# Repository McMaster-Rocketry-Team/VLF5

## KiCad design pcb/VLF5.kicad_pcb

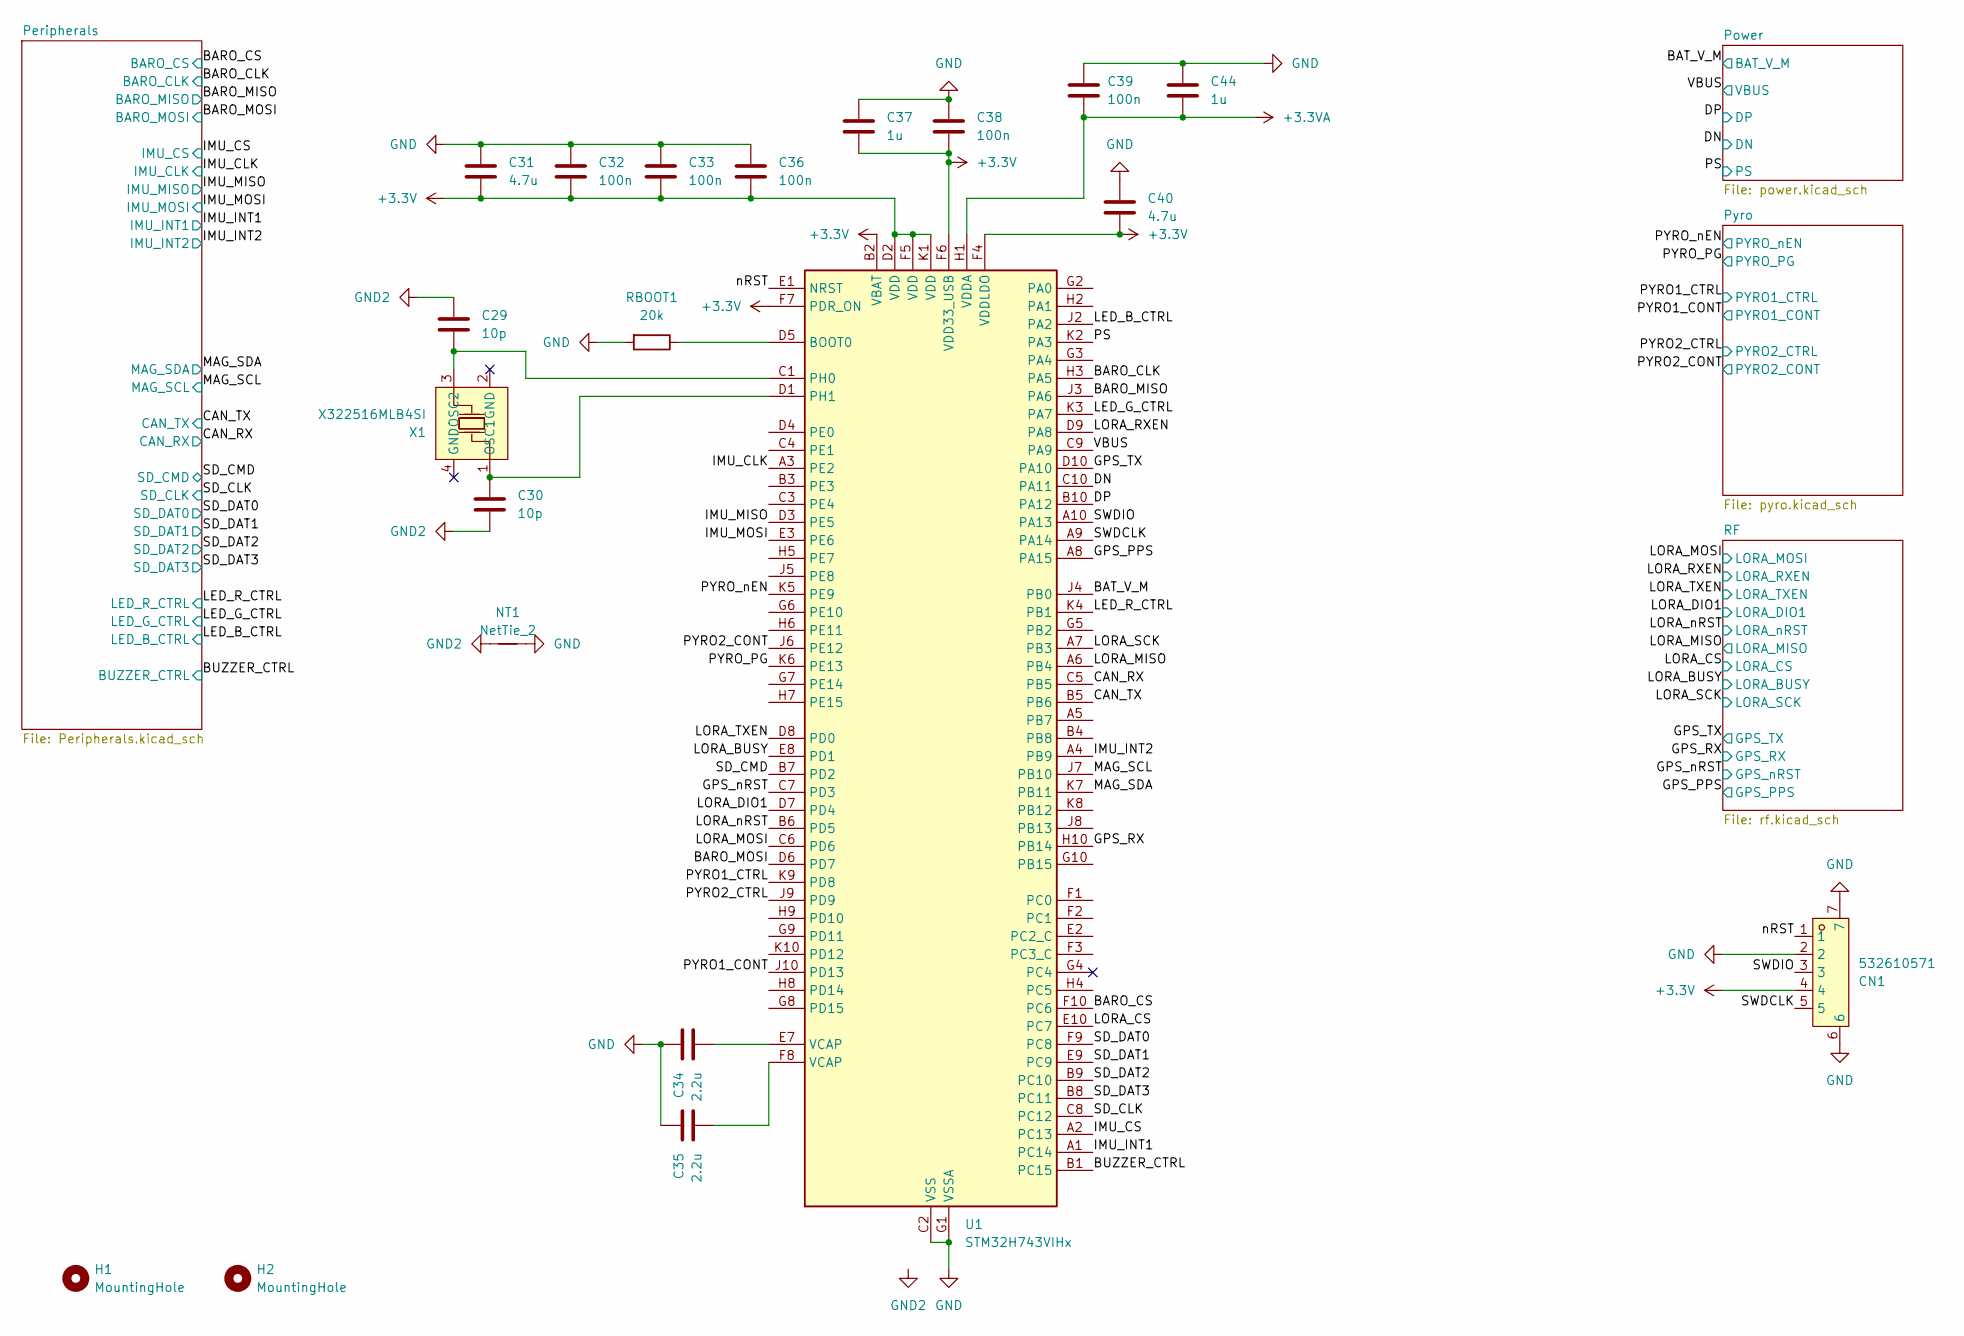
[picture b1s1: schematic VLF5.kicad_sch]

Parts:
C29, C30: 10p; C_0402_1005Metric
C31, C40: 4.7u; C_0402_1005Metric
C32, C33, C36, C38, C39: 100n; C_0402_1005Metric
C34, C35: 2.2u; C_0402_1005Metric
C37, C44: 1u; C_0402_1005Metric
CN1: 532610571; CONN-SMD_5P-P1.25_532610571-2; LCSC Part C392176
H1, H2: MountingHole; MountingHole_2.7mm_M2.5
NT1: NetTie_2; NetTie-2_SMD_Pad0.5mm
RBOOT1: 20k; R_0402_1005Metric
U1: STM32H743VIHx; TFBGA-100_8x8mm_Layout10x10_P0.8mm
X1: X322516MLB4SI; OSC-SMD_4P-L3.2-W2.5-BL; LCSC Part C13738

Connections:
+3.3V: C31.2, C32.2, C33.2, C36.2, C37.2, C38.2, C40.2, CN1.4, U1.B2 (VBAT), U1.D2 (VDD), U1.F4 (VDDLDO), U1.F5 (VDD), U1.F6 (VDD33_USB), U1.F7 (PDR_ON), U1.K1 (VDD); also elsewhere on the board
+3.3VA: C39.2, C44.2, U1.H1 (VDDA); also elsewhere on the board
/BARO_CLK: U1.H3 (PA5); also elsewhere on the board
/BARO_CS: U1.F10 (PC6); also elsewhere on the board
/BARO_MISO: U1.J3 (PA6); also elsewhere on the board
/BARO_MOSI: U1.D6 (PD7); also elsewhere on the board
/BAT_V_M: U1.J4 (PB0); also elsewhere on the board
/BUZZER_CTRL: U1.B1 (PC15); also elsewhere on the board
/CAN_RX: U1.C5 (PB5); also elsewhere on the board
/CAN_TX: U1.B5 (PB6); also elsewhere on the board
/DN: U1.C10 (PA11); also elsewhere on the board
/DP: U1.B10 (PA12); also elsewhere on the board
/GPS_PPS: U1.A8 (PA15); also elsewhere on the board
/GPS_RX: U1.H10 (PB14); also elsewhere on the board
/GPS_TX: U1.D10 (PA10); also elsewhere on the board
/GPS_nRST: U1.C7 (PD3); also elsewhere on the board
/IMU_CLK: U1.A3 (PE2); also elsewhere on the board
/IMU_CS: U1.A2 (PC13); also elsewhere on the board
/IMU_INT1: U1.A1 (PC14); also elsewhere on the board
/IMU_INT2: U1.A4 (PB9); also elsewhere on the board
/IMU_MISO: U1.D3 (PE5); also elsewhere on the board
/IMU_MOSI: U1.E3 (PE6); also elsewhere on the board
/LED_B_CTRL: U1.J2 (PA2); also elsewhere on the board
/LED_G_CTRL: U1.K3 (PA7); also elsewhere on the board
/LED_R_CTRL: U1.K4 (PB1); also elsewhere on the board
/LORA_BUSY: U1.E8 (PD1); also elsewhere on the board
/LORA_CS: U1.E10 (PC7); also elsewhere on the board
/LORA_DIO1: U1.D7 (PD4); also elsewhere on the board
/LORA_MISO: U1.A6 (PB4); also elsewhere on the board
/LORA_MOSI: U1.C6 (PD6); also elsewhere on the board
/LORA_RXEN: U1.D9 (PA8); also elsewhere on the board
/LORA_SCK: U1.A7 (PB3); also elsewhere on the board
/LORA_TXEN: U1.D8 (PD0); also elsewhere on the board
/LORA_nRST: U1.B6 (PD5); also elsewhere on the board
/MAG_SCL: U1.J7 (PB10); also elsewhere on the board
/MAG_SDA: U1.K7 (PB11); also elsewhere on the board
/PS: U1.K2 (PA3); also elsewhere on the board
/PYRO1_CONT: U1.J10 (PD13); also elsewhere on the board
/PYRO1_CTRL: U1.K9 (PD8); also elsewhere on the board
/PYRO2_CONT: U1.J6 (PE12); also elsewhere on the board
/PYRO2_CTRL: U1.J9 (PD9); also elsewhere on the board
/PYRO_PG: U1.K6 (PE13); also elsewhere on the board
/PYRO_nEN: U1.K5 (PE9); also elsewhere on the board
/SD_CLK: U1.C8 (PC12); also elsewhere on the board
/SD_CMD: U1.B7 (PD2); also elsewhere on the board
/SD_DAT0: U1.F9 (PC8); also elsewhere on the board
/SD_DAT1: U1.E9 (PC9); also elsewhere on the board
/SD_DAT2: U1.B9 (PC10); also elsewhere on the board
/SD_DAT3: U1.B8 (PC11); also elsewhere on the board
/SWDCLK: CN1.5, U1.A9 (PA14)
/SWDIO: CN1.3, U1.A10 (PA13)
/VBUS: U1.C9 (PA9); also elsewhere on the board
/nRST: CN1.1, U1.E1 (NRST)
unnamed: C34.2, U1.E7 (VCAP)
unnamed: C35.2, U1.F8 (VCAP)
unnamed: RBOOT1.1, U1.D5 (BOOT0)
unnamed: C29.2, U1.C1 (PH0), X1.3 (OSC2)
unnamed: C30.1, U1.D1 (PH1), X1.1 (OSC1)

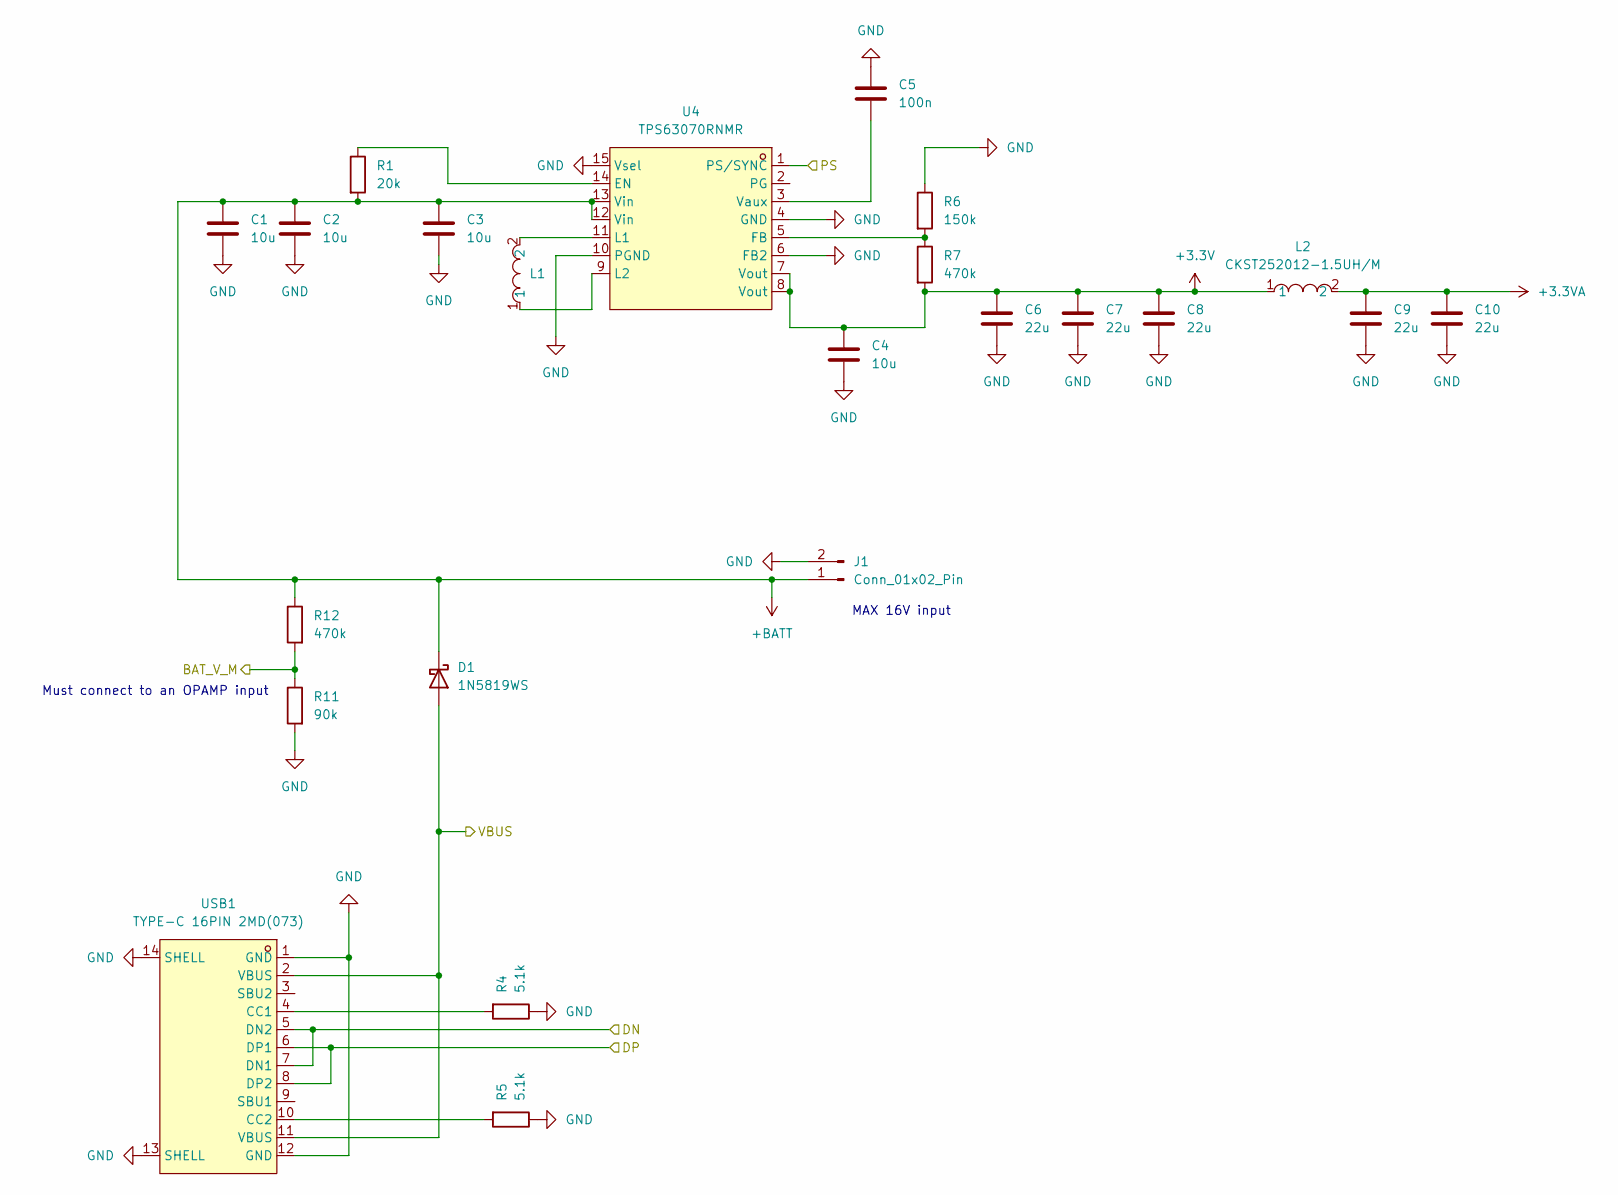
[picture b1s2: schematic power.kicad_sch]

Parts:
C1, C2, C3, C4: 10u; C_0603_1608Metric
C5: 100n; C_0402_1005Metric
C6, C7, C8, C9, C10: 22u; C_0603_1608Metric
D1: 1N5819WS; D_SOD-323
J1: Conn_01x02_Pin; 1054301102
L1, L2: CKST252012-1.5UH/M; IND-SMD_L2.5-W2.0-VLS252012CX-150M; LCSC Part C3002550
R1: 20k; R_0402_1005Metric
R4, R5: 5.1k; R_0402_1005Metric
R6: 150k; R_0402_1005Metric
R7, R12: 470k; R_0402_1005Metric
R11: 90k; R_0402_1005Metric
U4: TPS63070RNMR; VQFN-HR-15_L3.0-W2.5-P0.50-BL_TPS63070RNMR; LCSC Part C109322
USB1: TYPE-C 16PIN 2MD(073); USB-C-SMD_TYPE-C-6PIN-2MD-073; LCSC Part C2765186

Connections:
+3.3V: C4.2, C6.2, C7.2, C8.2, L2.1, R7.2, U4.7 (Vout), U4.8 (Vout); also elsewhere on the board
+3.3VA: C9.2, C10.2, L2.2; also elsewhere on the board
+BATT: C1.2, C2.2, C3.2, D1.1 (K), J1.1, J1.S2, R1.2, R12.1, U4.12 (Vin), U4.13 (Vin); also elsewhere on the board
/BAT_V_M: R11.1, R12.2; also elsewhere on the board
/DN: USB1.5 (DN2), USB1.7 (DN1); also elsewhere on the board
/DP: USB1.6 (DP1), USB1.8 (DP2); also elsewhere on the board
/PS: U4.1 (PS/SYNC); also elsewhere on the board
/VBUS: D1.2 (A), USB1.2 (VBUS), USB1.11 (VBUS); also elsewhere on the board
unnamed: R1.1, U4.14 (EN)
unnamed: R6.2, R7.1, U4.5 (FB)
unnamed: L1.2, U4.11 (L1)
unnamed: L1.1, U4.9 (L2)
unnamed: C5.1, U4.3 (Vaux)
unnamed: R4.2, USB1.4 (CC1)
unnamed: R5.2, USB1.10 (CC2)

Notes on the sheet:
Must connect to an OPAMP input
MAX 16V input

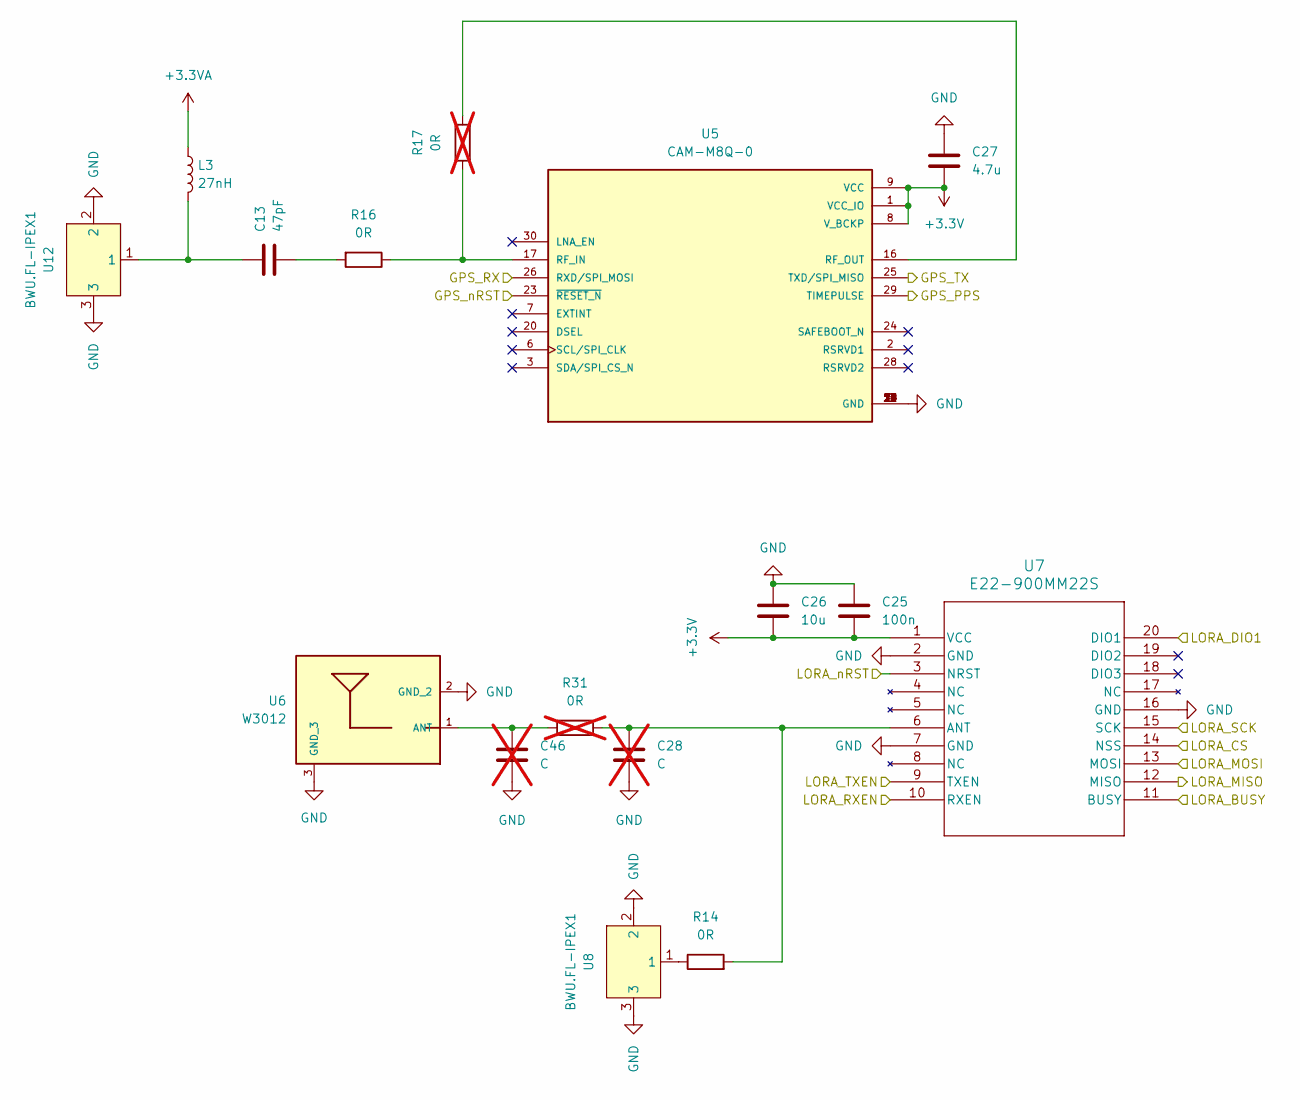
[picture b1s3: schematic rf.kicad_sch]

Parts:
C13: 47pF; C_0603_1608Metric_Pad1.08x0.95mm_HandSolder
C25: 100n; C_0402_1005Metric
C26: 10u; C_0603_1608Metric
C27: 4.7u; C_0402_1005Metric
C28, C46: C; C_0603_1608Metric_Pad1.08x0.95mm_HandSolder; not fitted
L3: 27nH; L_0603_1608Metric_Pad1.05x0.95mm_HandSolder
R14, R16: 0R; R_0603_1608Metric_Pad0.98x0.95mm_HandSolder
R17, R31: 0R; R_0603_1608Metric_Pad0.98x0.95mm_HandSolder; not fitted
U5: CAM-M8Q-0; LCC100P960X1400X210-31N
U6: W3012; W3012-ANT-PKG
U7: E22-900MM22S; E22-900MM22S_BYT
U8, U12: BWU.FL-IPEX1; IPEX-SMD_BWIPX-1-001E; LCSC Part C5137195

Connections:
+3.3V: C25.2, C26.2, C27.2, U5.1 (VCC_IO), U5.8 (V_BCKP), U5.9 (VCC), U7.1 (VCC); also elsewhere on the board
+3.3VA: L3.1; also elsewhere on the board
/GPS_PPS: U5.29 (TIMEPULSE); also elsewhere on the board
/GPS_RX: U5.26 (RXD/SPI_MOSI); also elsewhere on the board
/GPS_TX: U5.25 (TXD/SPI_MISO); also elsewhere on the board
/GPS_nRST: U5.23 (~RESET_N); also elsewhere on the board
/LORA_BUSY: U7.11 (BUSY); also elsewhere on the board
/LORA_CS: U7.14 (NSS); also elsewhere on the board
/LORA_DIO1: U7.20 (DIO1); also elsewhere on the board
/LORA_MISO: U7.12 (MISO); also elsewhere on the board
/LORA_MOSI: U7.13 (MOSI); also elsewhere on the board
/LORA_RXEN: U7.10 (RXEN); also elsewhere on the board
/LORA_SCK: U7.15 (SCK); also elsewhere on the board
/LORA_TXEN: U7.9 (TXEN); also elsewhere on the board
/LORA_nRST: U7.3 (NRST); also elsewhere on the board
unnamed: C13.1, L3.2, U12.1
unnamed: C13.2, R16.2
unnamed: R14.1, U8.1
unnamed: R16.1, R17.1, U5.17 (RF_IN)
unnamed: R17.2, U5.16 (RF_OUT)
unnamed: C46.1, R31.1, U6.1 (ANT)
unnamed: C28.1, R14.2, R31.2, U7.6 (ANT)

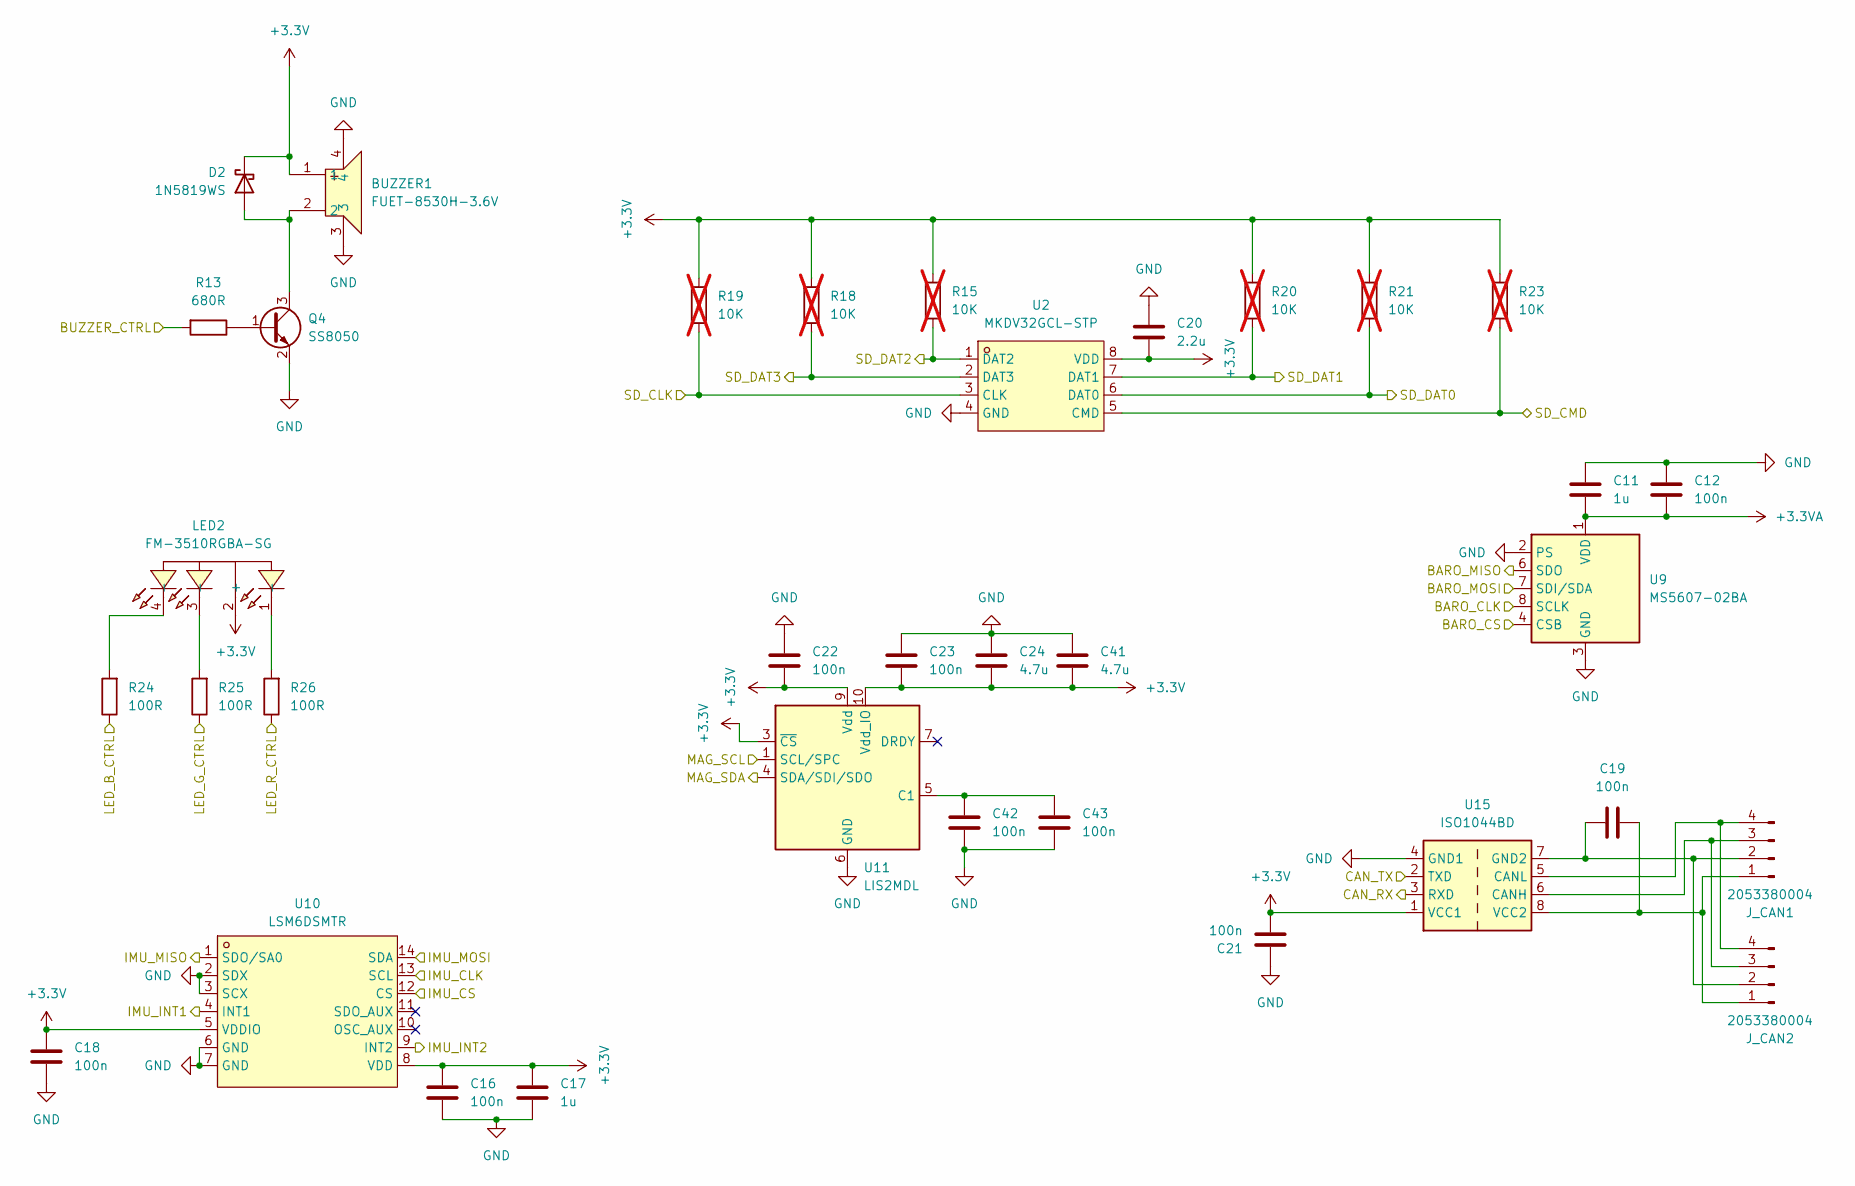
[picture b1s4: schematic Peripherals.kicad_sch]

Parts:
BUZZER1: FUET-8530H-3.6V; BUZ-SMD_4P-L8.5-W8.5_FUET-8530-05; LCSC Part C417429
C11, C17: 1u; C_0402_1005Metric
C12, C16, C18, C19, C21, C22, C23, C42, C43: 100n; C_0402_1005Metric
C20: 2.2u; C_0402_1005Metric
C24, C41: 4.7u; C_0402_1005Metric
D2: 1N5819WS; D_SOD-323
J_CAN1, J_CAN2: 2053380004; CONN_2053380000-SD_04_MOL
LED2: FM-3510RGBA-SG; LED-SMD_FM-3510RGBA-SG; LCSC Part C727903
Q4: SS8050; SOT-23
R13: 680R; R_0402_1005Metric
R15, R18, R19, R20, R21, R23: 10K; R_0603_1608Metric_Pad0.98x0.95mm_HandSolder; not fitted
R24, R25, R26: 100R; R_0402_1005Metric
U2: MKDV32GCL-STP; LGA-8_L6.0-W8.0-P1.27-TL; LCSC Part C7500179
U9: MS5607-02BA; LGA-8_3x5mm_P1.25mm
U10: LSM6DSMTR; LGA-14_L3.0-W2.5-P0.50-TL; LCSC Part C94048
U11: LIS2MDL; LGA-12_2x2mm_P0.5mm
U15: ISO1044BD; SOIC-8_3.9x4.9mm_P1.27mm

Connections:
+3.3V: BUZZER1.1, C16.1, C17.1, C18.1, C20.2, C21.2, C22.2, C23.2, C24.2, C41.2, D2.1 (K), LED2.2 (+), R15.2, R18.2, R19.2, R20.2, R21.2, R23.2, U2.8 (VDD), U10.5 (VDDIO), U10.8 (VDD), U11.3 (~CS), U11.9 (Vdd), U11.10 (Vdd_IO), U15.1 (VCC1); also elsewhere on the board
+3.3VA: C11.2, C12.2, U9.1 (VDD); also elsewhere on the board
/BARO_CLK: U9.8 (SCLK); also elsewhere on the board
/BARO_CS: U9.4 (CSB), U9.5 (CSB); also elsewhere on the board
/BARO_MISO: U9.6 (SDO); also elsewhere on the board
/BARO_MOSI: U9.7 (SDI/SDA); also elsewhere on the board
/BUZZER_CTRL: R13.2; also elsewhere on the board
/CAN_RX: U15.3 (RXD); also elsewhere on the board
/CAN_TX: U15.2 (TXD); also elsewhere on the board
/IMU_CLK: U10.13 (SCL); also elsewhere on the board
/IMU_CS: U10.12 (CS); also elsewhere on the board
/IMU_INT1: U10.4 (INT1); also elsewhere on the board
/IMU_INT2: U10.9 (INT2); also elsewhere on the board
/IMU_MISO: U10.1 (SDO/SA0); also elsewhere on the board
/IMU_MOSI: U10.14 (SDA); also elsewhere on the board
/LED_B_CTRL: R24.1; also elsewhere on the board
/LED_G_CTRL: R25.1; also elsewhere on the board
/LED_R_CTRL: R26.1; also elsewhere on the board
/MAG_SCL: U11.1 (SCL/SPC); also elsewhere on the board
/MAG_SDA: U11.4 (SDA/SDI/SDO); also elsewhere on the board
/SD_CLK: R19.1, U2.3 (CLK); also elsewhere on the board
/SD_CMD: R23.1, U2.5 (CMD); also elsewhere on the board
/SD_DAT0: R21.1, U2.6 (DAT0); also elsewhere on the board
/SD_DAT1: R20.1, U2.7 (DAT1); also elsewhere on the board
/SD_DAT2: R15.1, U2.1 (DAT2); also elsewhere on the board
/SD_DAT3: R18.1, U2.2 (DAT3); also elsewhere on the board
unnamed: BUZZER1.2, D2.2 (A), Q4.3 (C)
unnamed: C19.2, J_CAN1.1, J_CAN2.1, U15.8 (VCC2)
unnamed: C19.1, J_CAN1.2, J_CAN2.2, U15.7 (GND2)
unnamed: J_CAN1.3, J_CAN2.3, U15.6 (CANH)
unnamed: J_CAN1.4, J_CAN2.4, U15.5 (CANL)
unnamed 65: J_CAN1.6, J_CAN2.5; also elsewhere on the board
unnamed: LED2.1 (-), R26.2
unnamed: LED2.3 (-), R25.2
unnamed: LED2.4 (-), R24.2
unnamed: Q4.1 (B), R13.1
unnamed: C42.1, C43.1, U11.5 (C1)

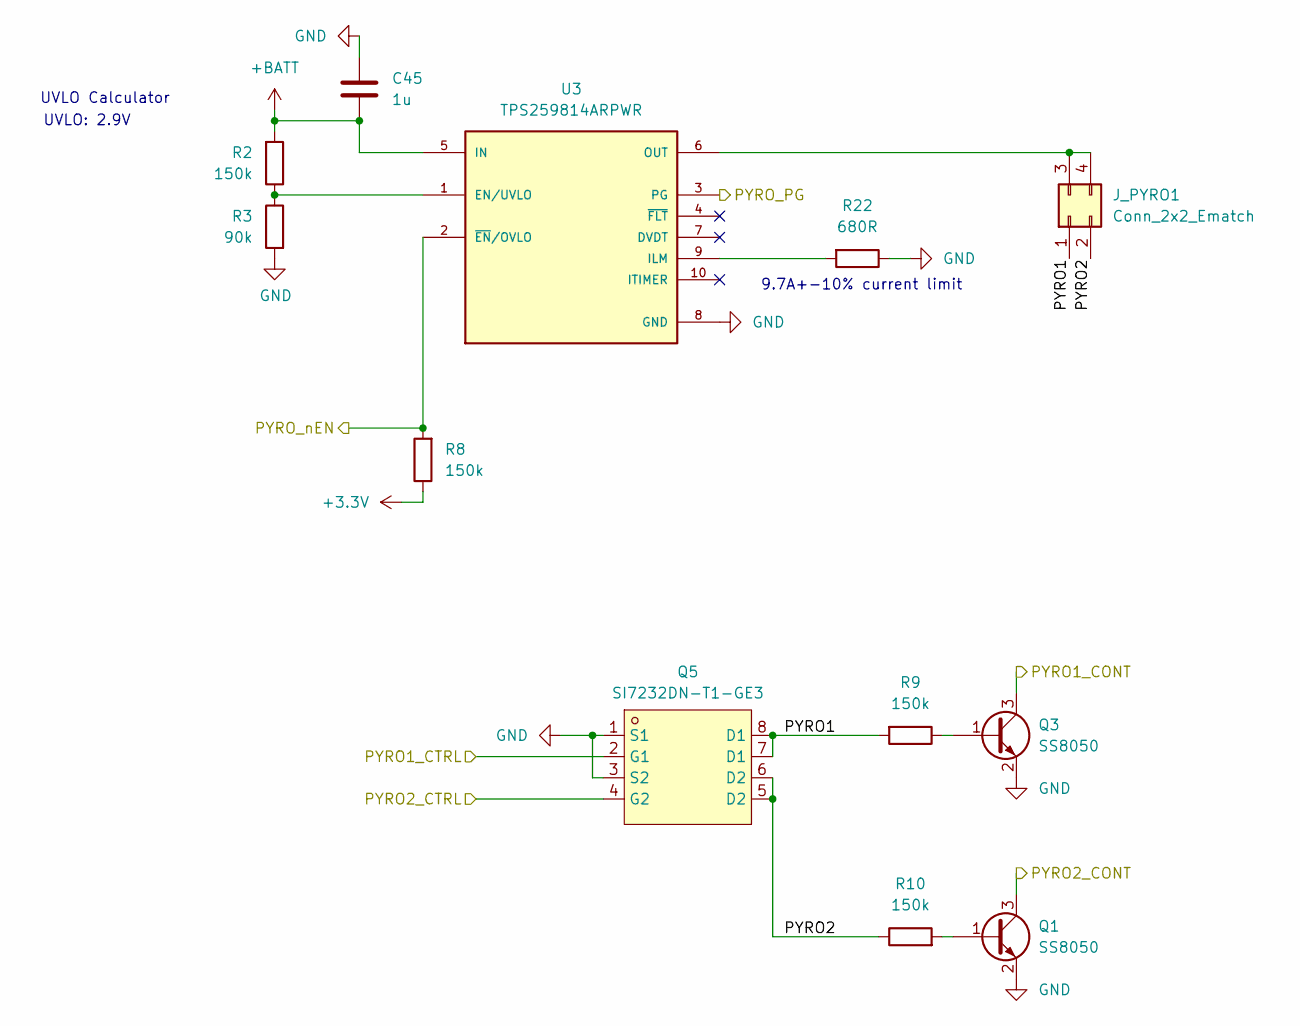
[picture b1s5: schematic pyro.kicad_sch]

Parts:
C45: 1u; C_0402_1005Metric
J_PYRO1: Conn_2x2_Ematch; 1054051104
Q1, Q3: SS8050; SOT-23
Q5: SI7232DN-T1-GE3; POWER-1212-8_L3.3-W3.3-P0.66-LS3.3-BL; LCSC Part C144854
R2, R8, R9, R10: 150k; R_0402_1005Metric
R3: 90k; R_0402_1005Metric
R22: 680R; R_0402_1005Metric
U3: TPS259814ARPWR; IC_TPS259814ARPWR; PARTREV A

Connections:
+3.3V: R8.1; also elsewhere on the board
+BATT: C45.2, R2.2, U3.5 (IN); also elsewhere on the board
/PYRO1_CONT: Q3.3 (C); also elsewhere on the board
/PYRO1_CTRL: Q5.2 (G1); also elsewhere on the board
/PYRO2_CONT: Q1.3 (C); also elsewhere on the board
/PYRO2_CTRL: Q5.4 (G2); also elsewhere on the board
/PYRO_PG: U3.3 (PG); also elsewhere on the board
/PYRO_nEN: R8.2, U3.2 (~EN/OVLO); also elsewhere on the board
/Pyro/PYRO1: J_PYRO1.1, Q5.7 (D1), Q5.8 (D1), R9.2
/Pyro/PYRO2: J_PYRO1.2, Q5.5 (D2), Q5.6 (D2), R10.1
unnamed 65: J_PYRO1.3, J_PYRO1.4, J_PYRO1.S1, U3.6 (OUT); also elsewhere on the board
unnamed: Q1.1 (B), R10.2
unnamed: Q3.1 (B), R9.1
unnamed: R2.1, R3.1, U3.1 (EN/UVLO)
unnamed: R22.2, U3.9 (ILM)

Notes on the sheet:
9.7A+-10% current limit
UVLO Calculator
UVLO: 2.9V

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
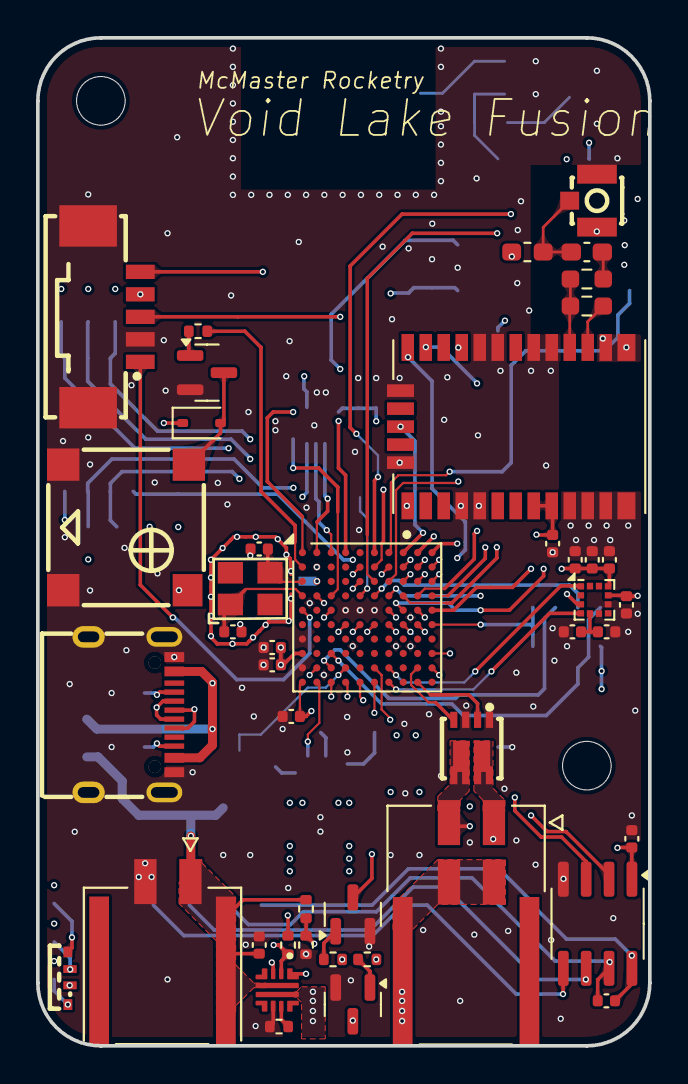
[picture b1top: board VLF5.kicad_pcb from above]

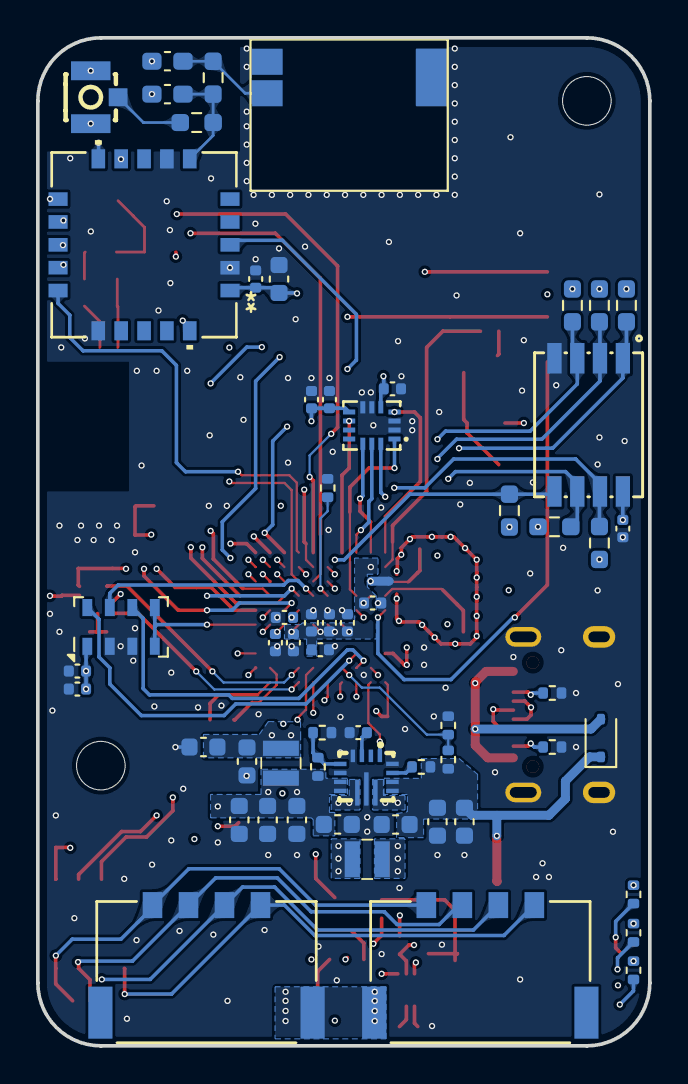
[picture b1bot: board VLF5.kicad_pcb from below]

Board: 6 copper layers, 34.0 x 56.0 mm, 105 parts (59 on the bottom side), 92 nets.

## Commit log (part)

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2025-03-19 added active gps antenna connector
2025-03-21 add pull up resistor for sd, change pad net
2025-03-31 Original Layout with Pins Configured
    🙏
2025-03-31 update cubemx
    updated cubemx
2025-03-31 Playing with configs Template
    As title describes
2025-04-01 Iterating
    Iterating
2025-04-01 Changed Pins new Layout
    Changed Pins new Layout
2025-04-01 Playing with Trace Configurations
    Still WIP!
2025-04-07 Saving for Edits
2025-04-07 Potential Layout 1
    - LDO in place?
2025-04-08 More Progress
    - Decoupling Capacitors Layed out
    - GPIO pins changed around for GPS and LoRa
    - STM Pin Vias Placed
    WARNING: ALTERED NO-NET PADS KEEP RESETTING TO NO-NET ENSURE NO ERRORS IN DRC.
2025-04-09 Committing Current Progress just in case
    As title describes
2025-04-10 More Routing
    Saving in case
2025-04-10 Playing with routing paths
    almost there
2025-04-10 About to change pins saving
    oh boy
2025-04-10 VLF5 Rough Finish
    Hallelujah
2025-04-10 cleanup
2025-04-19 setup clock
2025-04-26 beacon and gcm code
2025-04-27 update embassy
2025-04-27 refactor
2025-05-03 sd test
2025-05-04 tests
2025-05-05 imu and baro test
2025-05-06 pyro test
2025-05-06 mag test
2025-05-06 lora test
2025-05-06 updated cubemx
2025-05-09 imu noise test
2025-05-13 fix compile
2025-05-13 can test code
2025-05-13 change tick rate
2025-05-21 prepare for lora test
2025-05-21 can_main
2025-05-21 fix lora
2025-05-24 add rocket-cli
2025-05-24 use defmt_rtt_pipe
2025-06-01 main altimeter test
2025-06-01 fix warnings
2025-06-05 refactor beacon main
2025-06-05 refactor gcm code
2025-06-05 reafactor altimeter test code
2025-06-05 update main chute altitude
2025-06-05 add lora to altimeter test
2025-06-05 add missing slash
2025-06-05 altimeter test send continuity
2025-06-05 send agl altitude
2025-06-05 remove unused import
2025-06-21 bug fixes
2025-06-22 add blinky
2025-06-24 buzzer task and pyro task
2025-06-26 refactor file names
2025-06-26 more refactoring
2025-06-26 beacon
2025-07-13 fix compile errors, fire pyro option
2025-07-18 bootloader
2025-07-23 small changes
2025-07-24 avionics main wip
2025-07-24 can central
2025-07-24 receive vlp task
2025-07-25 low power mode
2025-07-25 landed mode
2025-07-25 unix clock
2025-07-25 broadcast unix time
2025-07-25 update can sender
2025-07-25 refactor can bus
2025-07-27 refactor VLCustomStatus
2025-08-04 fix build
2025-08-04 bootloader wip
2025-08-09 update imu driver
2025-08-10 imu test
2025-08-11 imu baro task
2025-08-12 armed mode
2025-08-12 refactor wip
2025-08-12 update can bus
2025-08-12 send AirBrakesControlMessage
2025-08-13 demo mode
2025-08-14 magnetometer
2025-08-15 self test mode and other changes
2025-08-15 buzzer
2025-08-15 bug fix
2025-08-17 default self test mode
2025-08-18 hardware in loop
2025-08-18 update flight profile
2025-08-19 stop camera after 15 min
2025-08-19 vl gcm
2025-08-19 fixes
2025-10-18 added logic to use a target apogee received by the gs
2025-10-21 changed target_agl to use a signal and noopmutex
2025-10-24 used watch instead of signal
2025-10-24 format
2025-11-05 basic control endpoint implementation
2025-11-05 define types
2025-11-05 remove unneccary dependency
2026-01-10 setup vscode for debugging
2026-01-10 update run config
2026-01-10 add readme
2026-01-10 update vscode settings
2026-01-15 Initialised SD card
2026-01-15 add rkyv example
2026-05-24 notes
2026-05-24 lockfile
2026-06-11 sd card flight logger
2026-06-11 patch embassy sdmmc dbckend
